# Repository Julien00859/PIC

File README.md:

# PIC
School project

## Schemas

## Contributors

* [Bastiaens Olivier](https://github.com/bastiaens)
* [Castiaux Julien](https://github.com/Julien00859)
* [Danthine Kevin](https://github.com/superuserC)
* [Petit Martin](https://github.com/NicoleEtLui)

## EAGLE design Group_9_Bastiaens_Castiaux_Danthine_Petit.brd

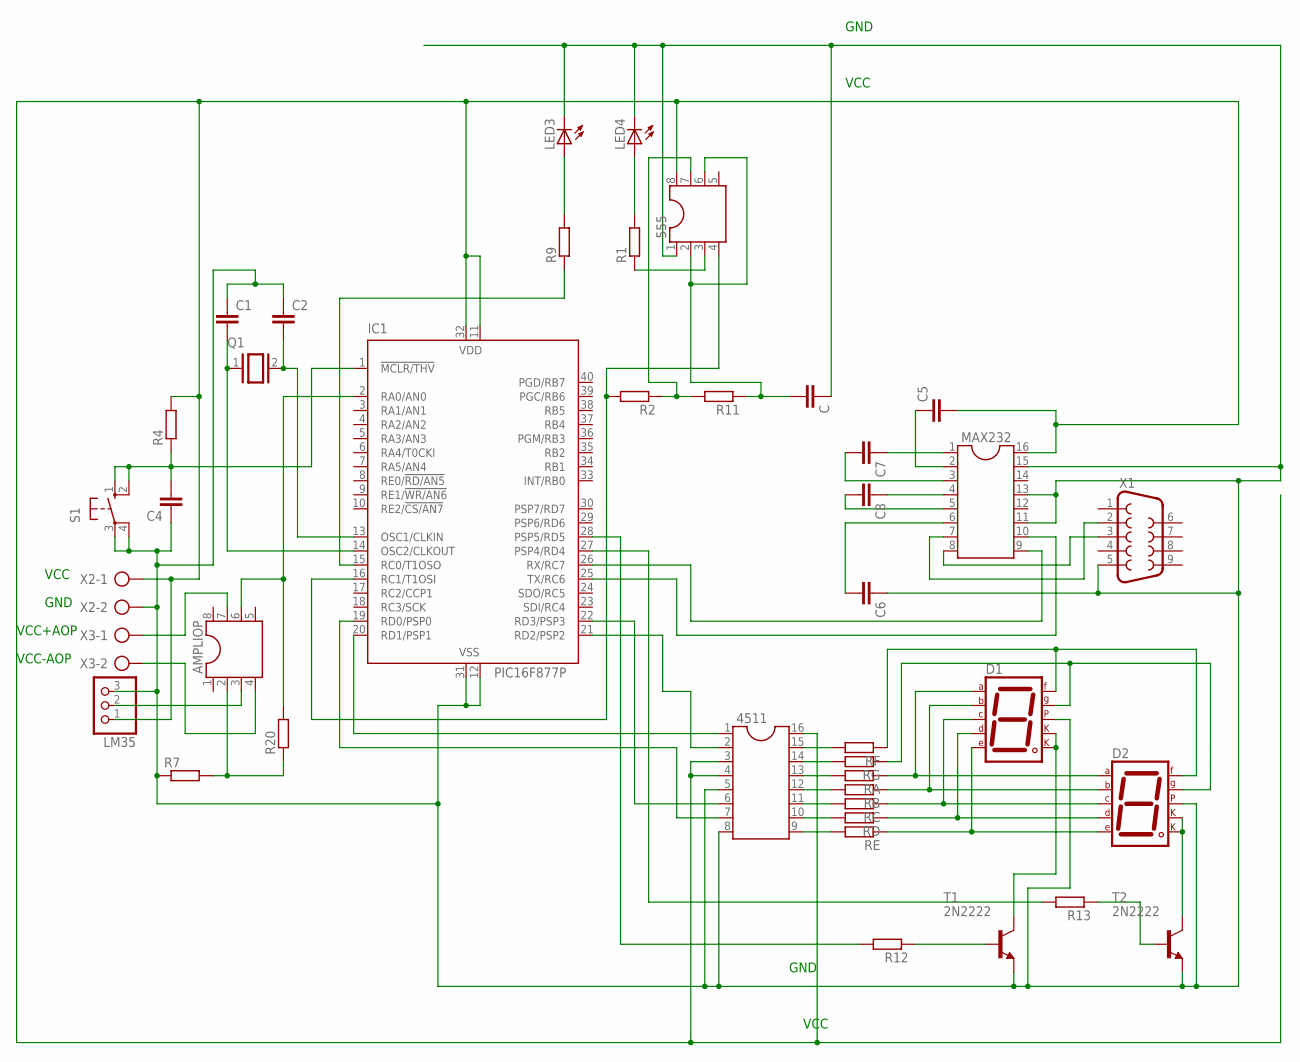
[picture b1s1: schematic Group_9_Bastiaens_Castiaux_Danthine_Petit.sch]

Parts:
555: DIL8; DIL08
4511: DIL16
AMPLIOP: DIL8; DIL08
C, C1, C2, C4, C5, C6, C7, C8: C-EU025-050X050; C025-050X050
D1, D2: 7SEG-CK; 7SEG-13
IC1: PIC16F877P; DIL40
LED3, LED4: LED_ELD260; LED_LD260
LM35: PINHD-1X3; 1X03
MAX232: DIL16
Q1: XTAL/S; QS
R1, R2, R4, R7, R9, R11, R12, R13, R20: R-EU_0204/7; 0204/7
RA: R-EU_0204/7; 0204/7
RB: R-EU_0204/7; 0204/7
RC: R-EU_0204/7; 0204/7
RD: R-EU_0204/7; 0204/7
RE: R-EU_0204/7; 0204/7
RF: R-EU_0204/7; 0204/7
RG: R-EU_0204/7; 0204/7
S1: 10-XX; B3F-10XX
T1, T2: 2N2222; TO18
X1: F09V
X2, X3: AK300/2

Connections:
GND: 555.1, 4511.5, 4511.8, C.1, C1.1, C2.1, C4.1, C6.1, D1.5 (DP), D2.5 (DP), IC1.12 (VSS), IC1.31 (VSS), LED3.K (C), LED4.K (C), LM35.3, MAX232.11, MAX232.13, MAX232.15, R7.1, S1.3, S1.4 (P1), T1.1 (E), T2.1 (E), X1.5, X2.2
unnamed: IC1.27 (PSP4/RD4), R13.2
unnamed: C1.2, IC1.14 (OSC2/CLKOUT), Q1.1
unnamed: AMPLIOP.2, R7.2, R20.1
unnamed: AMPLIOP.6, IC1.2 (RA0/AN0), R20.2
unnamed: AMPLIOP.3, LM35.2
unnamed: LED4.A, R1.2
unnamed: C4.2, IC1.1 (!MCLR/THV), R4.1, S1.1 (S), S1.2 (S1)
unnamed: C2.2, IC1.13 (OSC1/CLKIN), Q1.2
unnamed: 4511.1, IC1.20 (RD1/PSP1)
unnamed: LED3.A, R9.2
unnamed: 555.3, R1.1
unnamed: 555.2, 555.6, C.2, R11.1
unnamed: IC1.15 (RC0/T1OSO), R9.1
unnamed: 555.4, IC1.16 (RC1/T1OSI), R2.2
unnamed: MAX232.7, X1.2
unnamed: MAX232.8, X1.3
unnamed: C5.1, MAX232.2
unnamed: C7.1, MAX232.1
unnamed: C7.2, MAX232.3
unnamed: C8.1, MAX232.4
unnamed: C8.2, MAX232.5
unnamed: C6.2, MAX232.6
unnamed: IC1.25 (TX/RC6), MAX232.10
unnamed: IC1.26 (RX/RC7), MAX232.9
unnamed: 555.7, R2.1, R11.2
unnamed: 4511.7, IC1.19 (RD0/PSP0)
unnamed: D1.3 (CK1), D1.8 (CK2), T1.3 (C)
unnamed: 4511.2, IC1.21 (RD2/PSP2)
unnamed: 4511.6, IC1.22 (RD3/PSP3)
unnamed: 4511.13, RA.2
unnamed: IC1.28 (PSP5/RD5), R12.2
unnamed: 4511.12, RB.2
unnamed: 4511.11, RC.2
unnamed: 4511.10, RD.2
unnamed: 4511.9, RE.2
unnamed: D1.7 (A), D2.7 (A), RA.1
unnamed: D1.2 (D), D2.2 (D), RD.1
unnamed: D1.4 (C), D2.4 (C), RC.1
unnamed: D1.1 (E), D2.1 (E), RE.1
unnamed: 4511.15, RF.2
unnamed: 4511.14, RG.2
unnamed: AMPLIOP.7, X3.1
unnamed: D1.10 (G), D2.10 (G), RG.1
unnamed: R12.1, T1.2 (B)
unnamed: 555.8, 4511.3, 4511.4, 4511.16, C5.2, IC1.11 (VDD), IC1.32 (VDD), LM35.1, MAX232.16, R4.2, X2.1
unnamed: D2.3 (CK1), D2.8 (CK2), T2.3 (C)
unnamed: R13.1, T2.2 (B)
unnamed: AMPLIOP.4, X3.2
unnamed: D1.6 (B), D2.6 (B), RB.1
unnamed: D1.9 (F), D2.9 (F), RF.1

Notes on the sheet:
VCC
GND
VCC+AOP
VCC-AOP

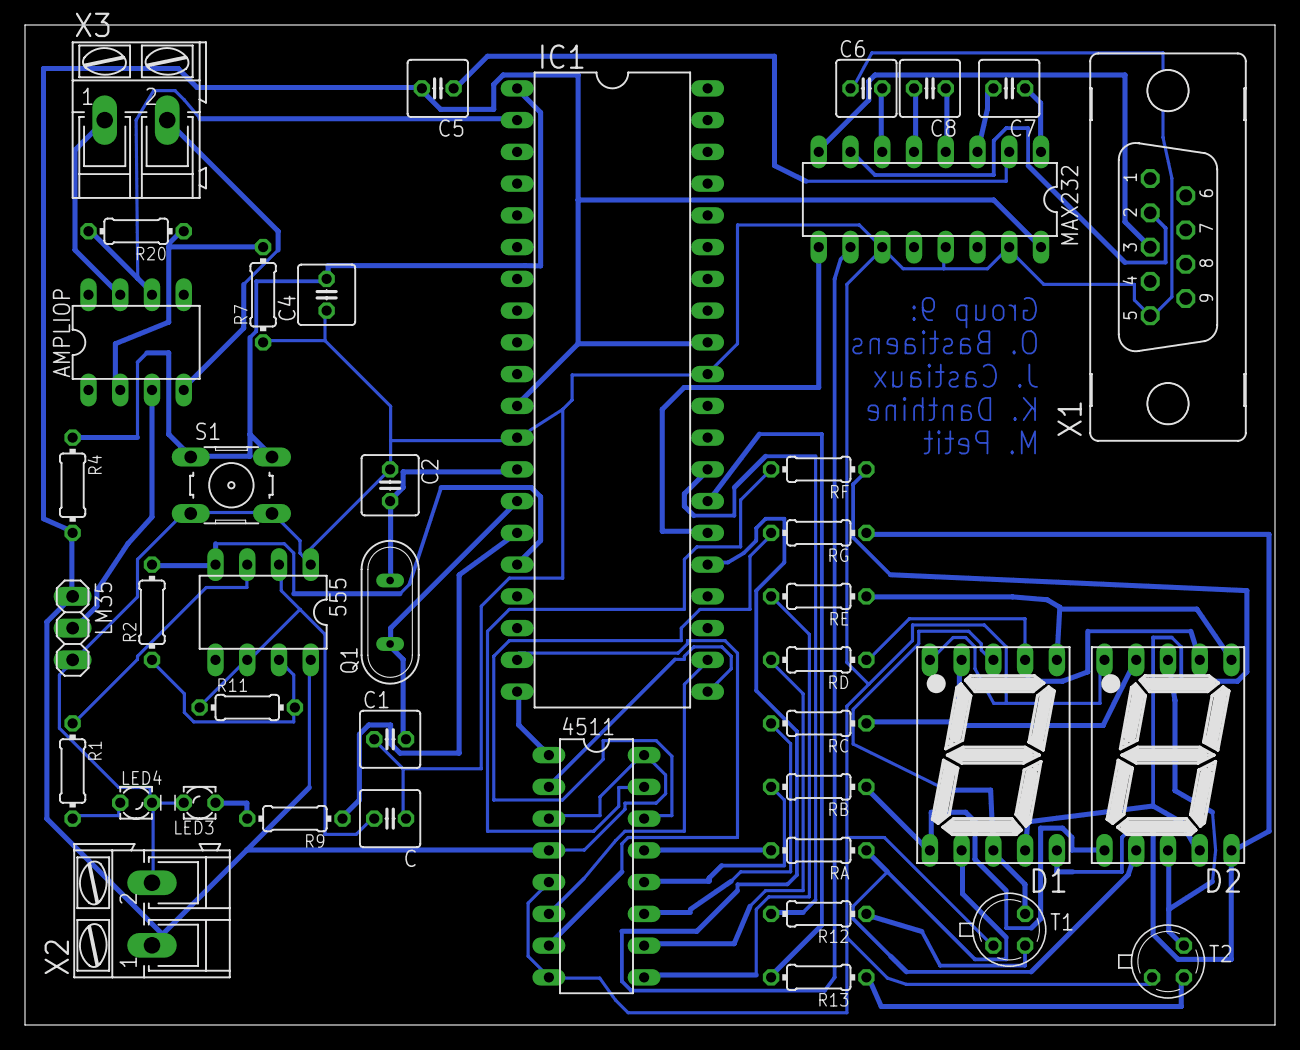
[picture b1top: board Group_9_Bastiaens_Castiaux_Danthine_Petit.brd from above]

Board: 2 copper layers, 100.0 x 80.0 mm, 41 parts (0 on the bottom side), 51 nets.

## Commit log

2017-02-12 PIC, Reset Button, Cristal Clock (20MHz), LEDs (red + green), Asatable 555 (blink red), 2 7-segment display with 2 decoders, Serial connector
2017-02-12 png export
2017-02-12 Use 7447 instead of 7448, C code to test the 7-seg display
2017-02-12 Update LICENSE
2017-02-15 ajout du code compilé
2017-02-17 add max232 (serial converter), lm35 (temperature probe), 471 (amplifier), use one decoder (4511 instead of 7447) for two 7-seg (common cathode instead of anode), fix the red led to be off when green 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
2017-02-17 add credits for kevin
2017-02-23 code source en C avec version compilee
2017-03-02 Ajout du schema sur Eagle
2017-03-03 Ajout interface rs232
2017-03-05 choix final du modele du pic + ajout de 4 condo max232 + suite schéma
2017-03-06 Application Java
2017-03-06 end of schematic connection 7seg finie
2017-03-07 schematic to pcb done 10% routing
2017-03-07 correction to board + plan de masse
2017-03-07 add eagle schema
2017-03-29 Create l
2017-05-11 schéma finaux - PIC <3
